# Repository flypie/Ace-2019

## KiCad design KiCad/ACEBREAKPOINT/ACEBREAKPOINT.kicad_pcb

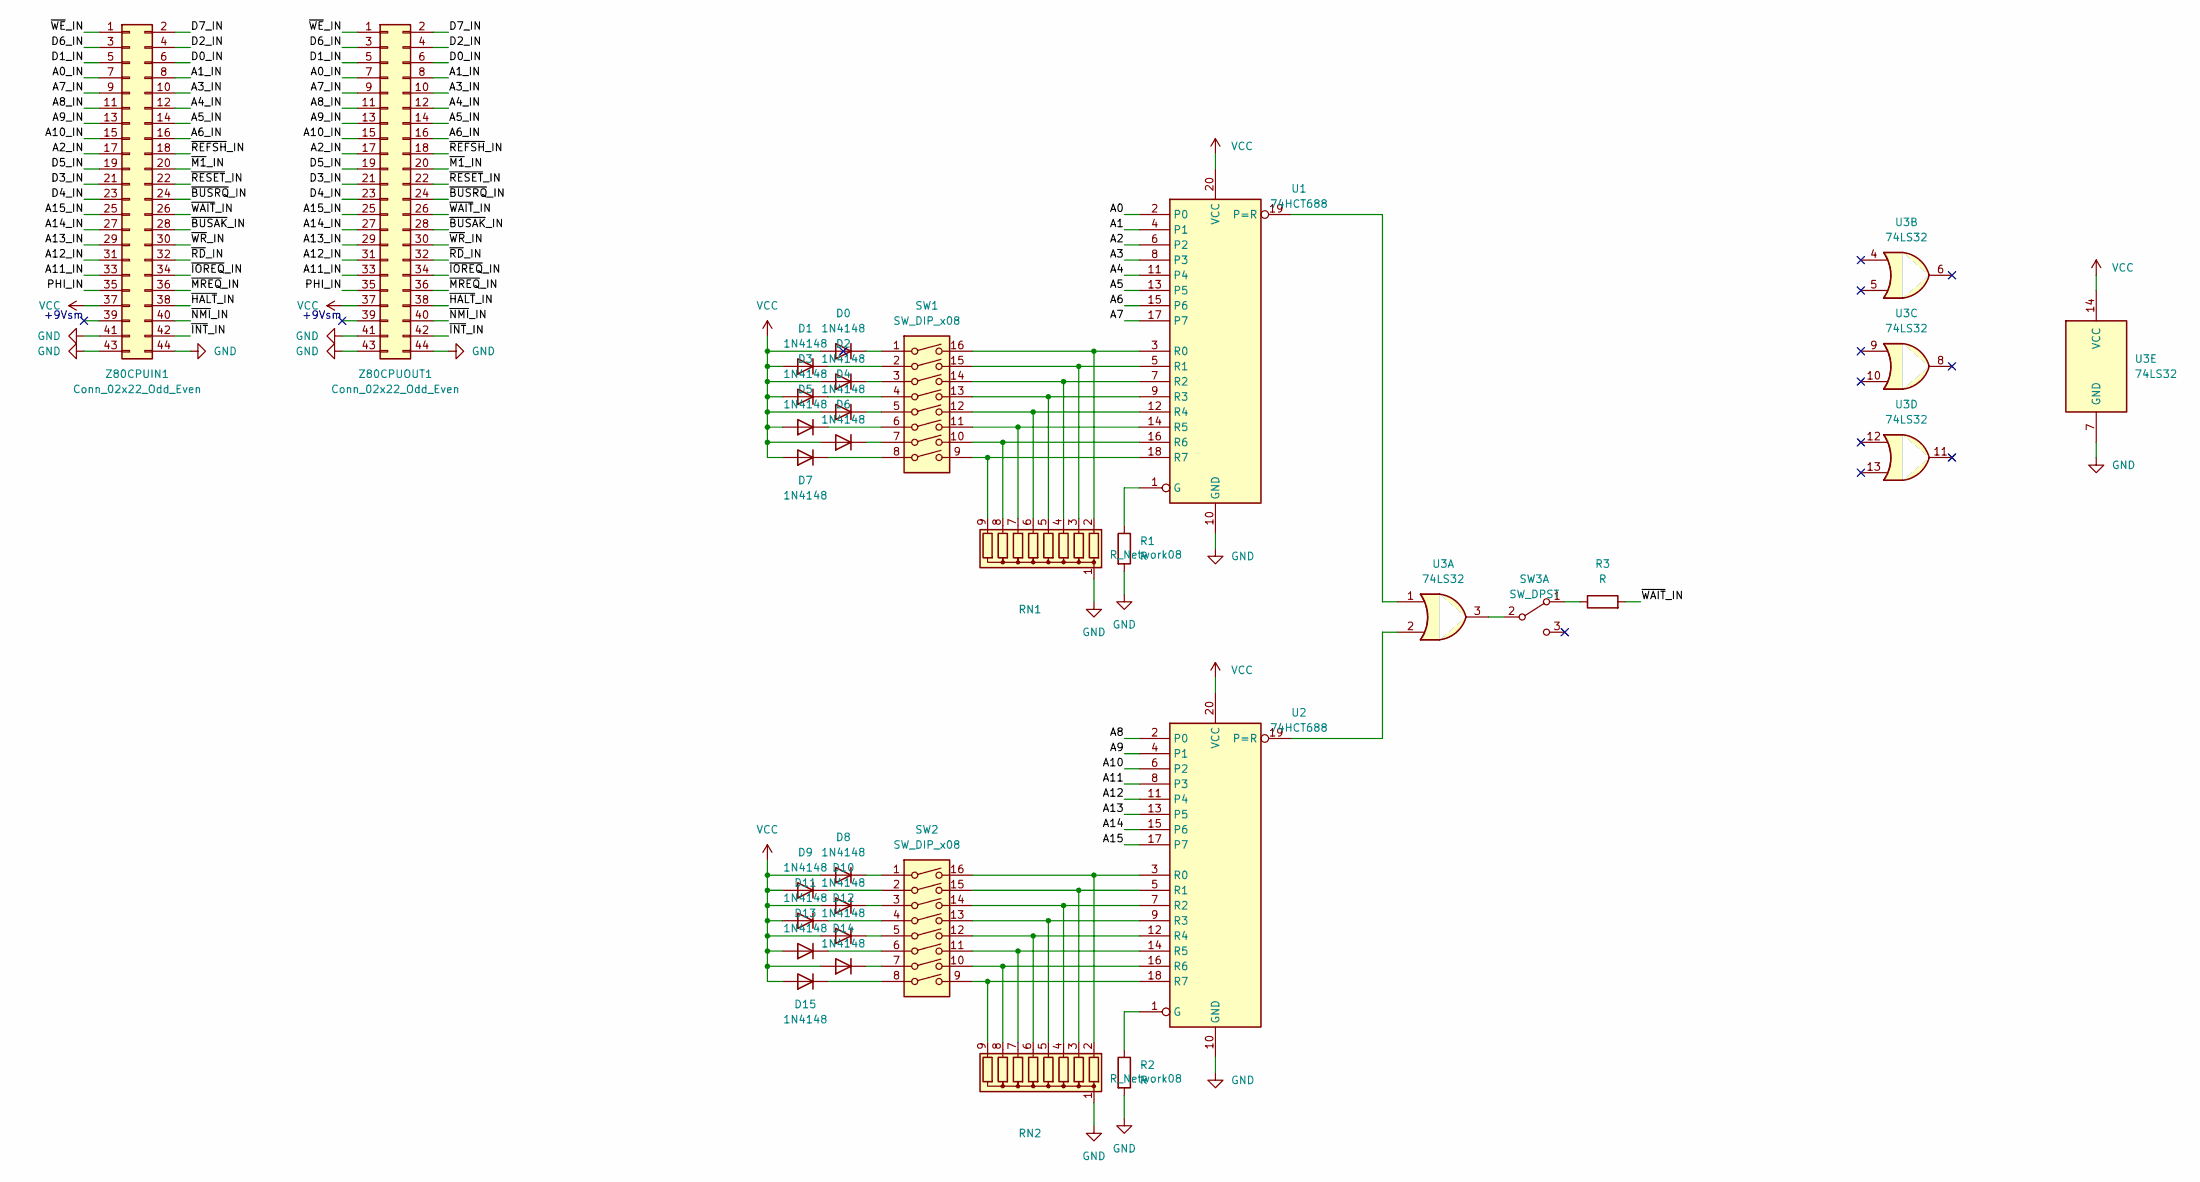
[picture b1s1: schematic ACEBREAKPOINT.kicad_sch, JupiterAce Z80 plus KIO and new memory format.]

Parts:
D0, D1, D2, D3, D4, D5, D6, D7, D8, D9, D10, D11, D12, D13, D14, D15: 1N4148; D_DO-35_SOD27_P2.54mm_Vertical_AnodeUp
R1, R2, R3: R; R_Axial_DIN0204_L3.6mm_D1.6mm_P1.90mm_Vertical
RN1, RN2: R_Network08; R_Array_SIP9
SW1, SW2: SW_DIP_x08; DIP-16_W7.62mm
SW3: SW_DPST; B13AP
U1, U2: 74HCT688; DIP-20_W7.62mm
U3: 74LS32; DIP-14_W7.62mm
Z80CPUIN1, Z80CPUOUT1: Conn_02x22_Odd_Even; PinHeader_2x22_P2.54mm_Vertical; Manufacturer_Part_Number M20-9721146

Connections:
/A0: U1.2 (P0)
/A0_IN: Z80CPUIN1.7, Z80CPUOUT1.7
/A1: U1.4 (P1)
/A1_IN: Z80CPUIN1.8, Z80CPUOUT1.8
/A2: U1.6 (P2)
/A2_IN: Z80CPUIN1.17, Z80CPUOUT1.17
/A3: U1.8 (P3)
/A3_IN: Z80CPUIN1.10, Z80CPUOUT1.10
/A4: U1.11 (P4)
/A4_IN: Z80CPUIN1.12, Z80CPUOUT1.12
/A5: U1.13 (P5)
/A5_IN: Z80CPUIN1.14, Z80CPUOUT1.14
/A6: U1.15 (P6)
/A6_IN: Z80CPUIN1.16, Z80CPUOUT1.16
/A7: U1.17 (P7)
/A7_IN: Z80CPUIN1.9, Z80CPUOUT1.9
/A8: U2.2 (P0)
/A8_IN: Z80CPUIN1.11, Z80CPUOUT1.11
/A9: U2.4 (P1)
/A9_IN: Z80CPUIN1.13, Z80CPUOUT1.13
/A10: U2.6 (P2)
/A10_IN: Z80CPUIN1.15, Z80CPUOUT1.15
/A11: U2.8 (P3)
/A11_IN: Z80CPUIN1.33, Z80CPUOUT1.33
/A12: U2.11 (P4)
/A12_IN: Z80CPUIN1.31, Z80CPUOUT1.31
/A13: U2.13 (P5)
/A13_IN: Z80CPUIN1.29, Z80CPUOUT1.29
/A14: U2.15 (P6)
/A14_IN: Z80CPUIN1.27, Z80CPUOUT1.27
/A15: U2.17 (P7)
/A15_IN: Z80CPUIN1.25, Z80CPUOUT1.25
/D0_IN: Z80CPUIN1.6, Z80CPUOUT1.6
/D1_IN: Z80CPUIN1.5, Z80CPUOUT1.5
/D2_IN: Z80CPUIN1.4, Z80CPUOUT1.4
/D3_IN: Z80CPUIN1.21, Z80CPUOUT1.21
/D4_IN: Z80CPUIN1.23, Z80CPUOUT1.23
/D5_IN: Z80CPUIN1.19, Z80CPUOUT1.19
/D6_IN: Z80CPUIN1.3, Z80CPUOUT1.3
/D7_IN: Z80CPUIN1.2, Z80CPUOUT1.2
/PHI_IN: Z80CPUIN1.35, Z80CPUOUT1.35
/~BUSAK_IN: Z80CPUIN1.28, Z80CPUOUT1.28
/~BUSRQ_IN: Z80CPUIN1.24, Z80CPUOUT1.24
/~HALT_IN: Z80CPUIN1.38, Z80CPUOUT1.38
/~INT_IN: Z80CPUIN1.42, Z80CPUOUT1.42
/~IOREQ_IN: Z80CPUIN1.34, Z80CPUOUT1.34
/~M1_IN: Z80CPUIN1.20, Z80CPUOUT1.20
/~MREQ_IN: Z80CPUIN1.36, Z80CPUOUT1.36
/~NMI_IN: Z80CPUIN1.40, Z80CPUOUT1.40
/~RD_IN: Z80CPUIN1.32, Z80CPUOUT1.32
/~REFSH_IN: Z80CPUIN1.18, Z80CPUOUT1.18
/~RESET_IN: Z80CPUIN1.22, Z80CPUOUT1.22
/~WAIT_IN: R3.2, Z80CPUIN1.26, Z80CPUOUT1.26
/~WE_IN: Z80CPUIN1.1, Z80CPUOUT1.1
/~WR_IN: Z80CPUIN1.30, Z80CPUOUT1.30
GND: R1.2, R2.2, RN1.1 (common), RN2.1 (common), U1.10 (GND), U2.10 (GND), U3.7 (GND), Z80CPUIN1.41, Z80CPUIN1.43, Z80CPUIN1.44, Z80CPUOUT1.41, Z80CPUOUT1.43, Z80CPUOUT1.44
unnamed: D0.1 (K), SW1.1
unnamed: D1.1 (K), SW1.2
unnamed: D2.1 (K), SW1.3
unnamed: D3.1 (K), SW1.4
unnamed: D4.1 (K), SW1.5
unnamed: D5.1 (K), SW1.6
unnamed: D6.1 (K), SW1.7
unnamed: D7.1 (K), SW1.8
unnamed: D8.1 (K), SW2.1
unnamed: D9.1 (K), SW2.2
unnamed: D10.1 (K), SW2.3
unnamed: D11.1 (K), SW2.4
unnamed: D12.1 (K), SW2.5
unnamed: D13.1 (K), SW2.6
unnamed: D14.1 (K), SW2.7
unnamed: D15.1 (K), SW2.8
unnamed: R1.1, U1.1 (G)
unnamed: R2.1, U2.1 (G)
unnamed: R3.1, SW3.1 (A)
unnamed: RN1.2 (R1), SW1.16, U1.3 (R0)
unnamed: RN1.3 (R2), SW1.15, U1.5 (R1)
unnamed: RN1.4 (R3), SW1.14, U1.7 (R2)
unnamed: RN1.5 (R4), SW1.13, U1.9 (R3)
unnamed: RN1.6 (R5), SW1.12, U1.12 (R4)
unnamed: RN1.7 (R6), SW1.11, U1.14 (R5)
unnamed: RN1.8 (R7), SW1.10, U1.16 (R6)
unnamed: RN1.9 (R8), SW1.9, U1.18 (R7)
unnamed: RN2.2 (R1), SW2.16, U2.3 (R0)
unnamed: RN2.3 (R2), SW2.15, U2.5 (R1)
unnamed: RN2.4 (R3), SW2.14, U2.7 (R2)
unnamed: RN2.5 (R4), SW2.13, U2.9 (R3)
unnamed: RN2.6 (R5), SW2.12, U2.12 (R4)
unnamed: RN2.7 (R6), SW2.11, U2.14 (R5)
unnamed: RN2.8 (R7), SW2.10, U2.16 (R6)
unnamed: RN2.9 (R8), SW2.9, U2.18 (R7)
unnamed: U1.19 (P=R), U3.1
unnamed: U2.19 (P=R), U3.2
unnamed: SW3.2 (B), U3.3
VCC: D0.2 (A), D1.2 (A), D2.2 (A), D3.2 (A), D4.2 (A), D5.2 (A), D6.2 (A), D7.2 (A), D8.2 (A), D9.2 (A), D10.2 (A), D11.2 (A), D12.2 (A), D13.2 (A), D14.2 (A), D15.2 (A), U1.20 (VCC), U2.20 (VCC), U3.14 (VCC), Z80CPUIN1.37, Z80CPUOUT1.37

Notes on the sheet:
+9Vsm

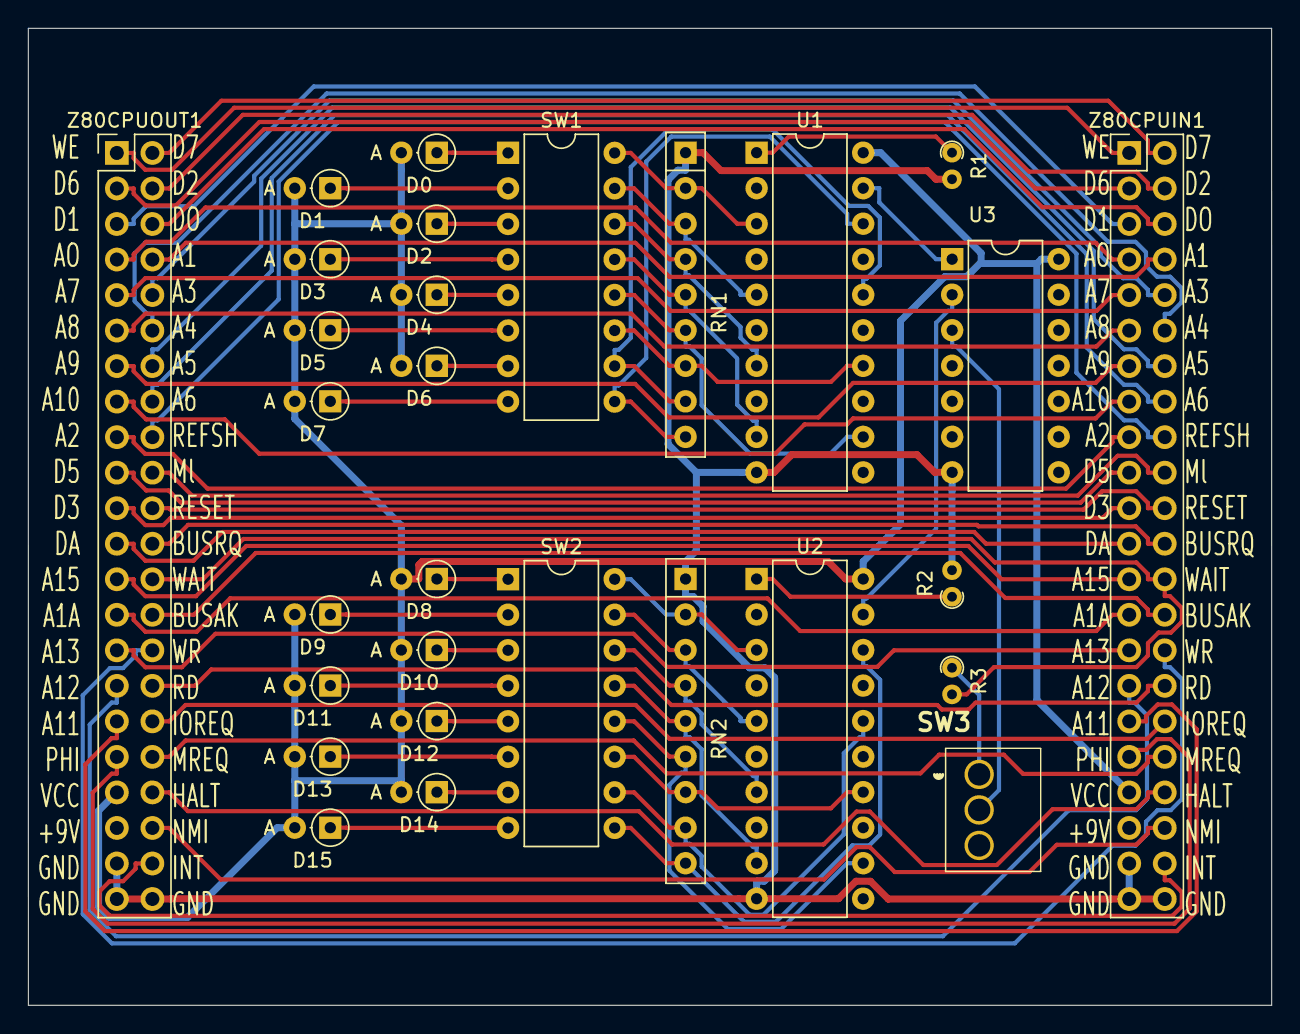
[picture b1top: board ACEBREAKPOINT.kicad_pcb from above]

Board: 2 copper layers, 88.9 x 69.8 mm, 29 parts (0 on the bottom side), 79 nets.

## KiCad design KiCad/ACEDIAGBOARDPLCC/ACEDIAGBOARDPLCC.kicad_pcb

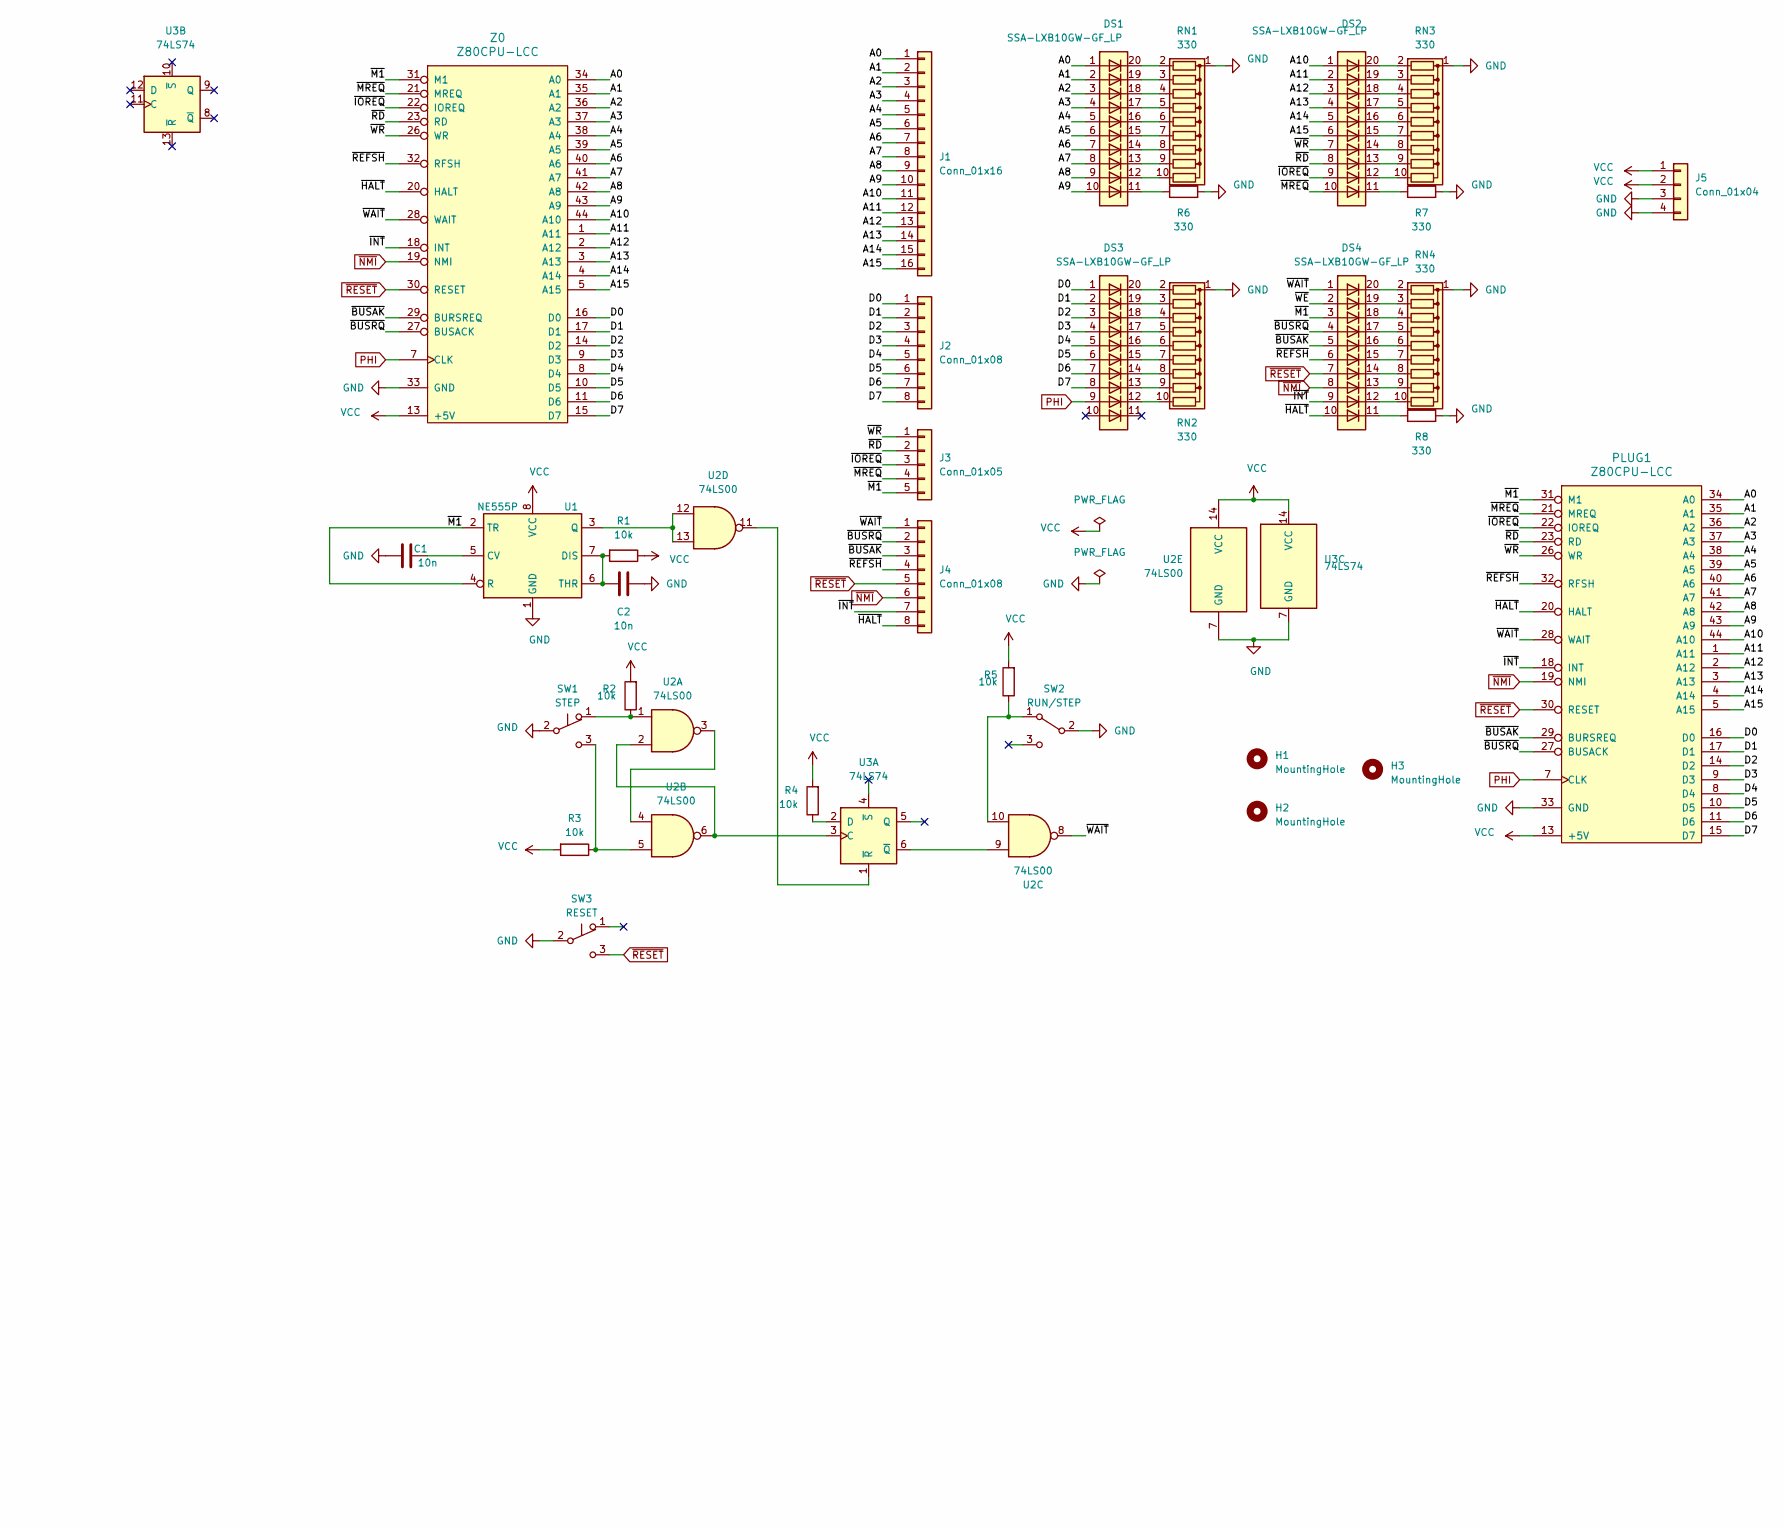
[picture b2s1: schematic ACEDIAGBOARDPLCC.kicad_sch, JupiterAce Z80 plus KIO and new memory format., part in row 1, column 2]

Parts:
C1, C2: 10n; C_Disc_D4.7mm_W2.5mm_P5.00mm
DS1, DS2, DS3, DS4: SSA-LXB10GW-GF_LP; 10_Bar_LED_Array_DIP-20_W7.62mm; Manufacturer_Part_Number SSA-LXB10GW-GF/LP; Mouser Part Number 696-SSA-LXB10GW
H1, H2, H3: MountingHole; MountingHole_3.5mm
J1: Conn_01x16; PinHeader_1x16_P2.54mm_Vertical
J2, J4: Conn_01x08; PinHeader_1x08_P2.54mm_Vertical
J3: Conn_01x05; PinHeader_1x05_P2.54mm_Vertical
J5: Conn_01x04; PinHeader_1x04_P2.54mm_Vertical
PLUG1: Z80CPU-LCC; PLCC-44_16.6x16.6mm_P1.27mm Mirror; Manufacturer_Part_Number W9382-ZC170
R1, R2, R3, R4, R5: 10k; R_Axial_DIN0204_L3.6mm_D1.6mm_P1.90mm_Vertical
R6, R7, R8: 330; R_Axial_DIN0204_L3.6mm_D1.6mm_P1.90mm_Vertical
RN1, RN2, RN3, RN4: 330; R_Array_SIP10; Manufacturer_Part_Number 4610X-101-331LF
SW1: STEP; ZMAXXXYYYZZZLC
SW2: RUN/STEP; B13AP
SW3: RESET; ZMAXXXYYYZZZLC
U1: NE555P; DIP-8_W7.62mm
U2: 74LS00; DIP-14_W7.62mm
U3: 74LS74; DIP-14_W7.62mm
Z0: Z80CPU-LCC; PLCC-44_THT-Socket; Manufacturer_Part_Number Z84C00

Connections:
/A0: DS1.1 (A), J1.1, PLUG1.34 (A0), Z0.34 (A0)
/A1: DS1.2 (A), J1.2, PLUG1.35 (A1), Z0.35 (A1)
/A2: DS1.3 (A), J1.3, PLUG1.36 (A2), Z0.36 (A2)
/A3: DS1.4 (A), J1.4, PLUG1.37 (A3), Z0.37 (A3)
/A4: DS1.5 (A), J1.5, PLUG1.38 (A4), Z0.38 (A4)
/A5: DS1.6 (A), J1.6, PLUG1.39 (A5), Z0.39 (A5)
/A6: DS1.7 (A), J1.7, PLUG1.40 (A6), Z0.40 (A6)
/A7: DS1.8 (A), J1.8, PLUG1.41 (A7), Z0.41 (A7)
/A8: DS1.9 (A), J1.9, PLUG1.42 (A8), Z0.42 (A8)
/A9: DS1.10 (A), J1.10, PLUG1.43 (A9), Z0.43 (A9)
/A10: DS2.1 (A), J1.11, PLUG1.44 (A10), Z0.44 (A10)
/A11: DS2.2 (A), J1.12, PLUG1.1 (A11), Z0.1 (A11)
/A12: DS2.3 (A), J1.13, PLUG1.2 (A12), Z0.2 (A12)
/A13: DS2.4 (A), J1.14, PLUG1.3 (A13), Z0.3 (A13)
/A14: DS2.5 (A), J1.15, PLUG1.4 (A14), Z0.4 (A14)
/A15: DS2.6 (A), J1.16, PLUG1.5 (A15), Z0.5 (A15)
/D0: DS3.1 (A), J2.1, PLUG1.16 (D0), Z0.16 (D0)
/D1: DS3.2 (A), J2.2, PLUG1.17 (D1), Z0.17 (D1)
/D2: DS3.3 (A), J2.3, PLUG1.14 (D2), Z0.14 (D2)
/D3: DS3.4 (A), J2.4, PLUG1.9 (D3), Z0.9 (D3)
/D4: DS3.5 (A), J2.5, PLUG1.8 (D4), Z0.8 (D4)
/D5: DS3.6 (A), J2.6, PLUG1.10 (D5), Z0.10 (D5)
/D6: DS3.7 (A), J2.7, PLUG1.11 (D6), Z0.11 (D6)
/D7: DS3.8 (A), J2.8, PLUG1.15 (D7), Z0.15 (D7)
/~BUSAK: DS4.5 (A), J4.3, PLUG1.29 (BURSREQ), Z0.29 (BURSREQ)
/~BUSRQ: DS4.4 (A), J4.2, PLUG1.27 (BUSACK), Z0.27 (BUSACK)
/~HALT: DS4.10 (A), J4.8, PLUG1.20 (HALT), Z0.20 (HALT)
/~INT: DS4.9 (A), J4.7, PLUG1.18 (INT), Z0.18 (INT)
/~IOREQ: DS2.9 (A), J3.3, PLUG1.22 (IOREQ), Z0.22 (IOREQ)
/~M1: DS4.3 (A), J3.5, PLUG1.31 (M1), U1.2 (TR), U1.4 (R), Z0.31 (M1)
/~MREQ: DS2.10 (A), J3.4, PLUG1.21 (MREQ), Z0.21 (MREQ)
/~RD: DS2.8 (A), J3.2, PLUG1.23 (RD), Z0.23 (RD)
/~REFSH: DS4.6 (A), J4.4, PLUG1.32 (RFSH), Z0.32 (RFSH)
/~WAIT: DS4.1 (A), J4.1, PLUG1.28 (WAIT), U2.8, Z0.28 (WAIT)
/~WE: DS4.2 (A)
/~WR: DS2.7 (A), J3.1, PLUG1.26 (WR), Z0.26 (WR)
GND: C1.2, C2.1, J5.3, J5.4, PLUG1.33 (GND), R6.2, R7.2, R8.2, RN1.1 (common), RN2.1 (common), RN3.1 (common), RN4.1 (common), SW1.2 (B), SW2.2 (B), SW3.2 (B), U1.1 (GND), U2.7 (GND), U3.7 (GND), Z0.33 (GND)
unnamed: C1.1, U1.5 (CV)
unnamed: C2.2, R1.2, U1.6 (THR), U1.7 (DIS)
unnamed: DS1.11 (K), R6.1
unnamed: DS1.12 (K), RN1.10 (R9)
unnamed: DS1.13 (K), RN1.9 (R8)
unnamed: DS1.14 (K), RN1.8 (R7)
unnamed: DS1.15 (K), RN1.7 (R6)
unnamed: DS1.16 (K), RN1.6 (R5)
unnamed: DS1.17 (K), RN1.5 (R4)
unnamed: DS1.18 (K), RN1.4 (R3)
unnamed: DS1.19 (K), RN1.3 (R2)
unnamed: DS1.20 (K), RN1.2 (R1)
unnamed: DS2.11 (K), R7.1
unnamed: DS2.12 (K), RN3.10 (R9)
unnamed: DS2.13 (K), RN3.9 (R8)
unnamed: DS2.14 (K), RN3.8 (R7)
unnamed: DS2.15 (K), RN3.7 (R6)
unnamed: DS2.16 (K), RN3.6 (R5)
unnamed: DS2.17 (K), RN3.5 (R4)
unnamed: DS2.18 (K), RN3.4 (R3)
unnamed: DS2.19 (K), RN3.3 (R2)
unnamed: DS2.20 (K), RN3.2 (R1)
unnamed: DS3.12 (K), RN2.10 (R9)
unnamed: DS3.13 (K), RN2.9 (R8)
unnamed: DS3.14 (K), RN2.8 (R7)
unnamed: DS3.15 (K), RN2.7 (R6)
unnamed: DS3.16 (K), RN2.6 (R5)
unnamed: DS3.17 (K), RN2.5 (R4)
unnamed: DS3.18 (K), RN2.4 (R3)
unnamed: DS3.19 (K), RN2.3 (R2)
unnamed: DS3.20 (K), RN2.2 (R1)
unnamed: DS4.11 (K), R8.1
unnamed: DS4.12 (K), RN4.10 (R9)
unnamed: DS4.13 (K), RN4.9 (R8)
unnamed: DS4.14 (K), RN4.8 (R7)
unnamed: DS4.15 (K), RN4.7 (R6)
unnamed: DS4.16 (K), RN4.6 (R5)
unnamed: DS4.17 (K), RN4.5 (R4)
unnamed: DS4.18 (K), RN4.4 (R3)
unnamed: DS4.19 (K), RN4.3 (R2)
unnamed: DS4.20 (K), RN4.2 (R1)
unnamed: R2.1, SW1.1 (A), U2.1
unnamed: R3.1, SW1.3 (C), U2.5
unnamed: R4.1, U3.2 (D)
unnamed: R5.1, SW2.1 (A), U2.10
unnamed: U1.3 (Q), U2.12, U2.13
unnamed: U2.2, U2.6, U3.3 (C)
unnamed: U2.3, U2.4
unnamed: U2.9, U3.6 (~Q)
unnamed: U2.11, U3.1 (~R)
PHI: DS3.9 (A), PLUG1.7 (CLK), Z0.7 (CLK)
VCC: J5.1, J5.2, PLUG1.13 (+5V), R1.1, R2.2, R3.2, R4.2, R5.2, U1.8 (VCC), U2.14 (VCC), U3.14 (VCC), Z0.13 (+5V)
~NMI: DS4.8 (A), J4.6, PLUG1.19 (NMI), Z0.19 (NMI)
~RESET: DS4.7 (A), J4.5, PLUG1.30 (RESET), SW3.3 (C), Z0.30 (RESET)

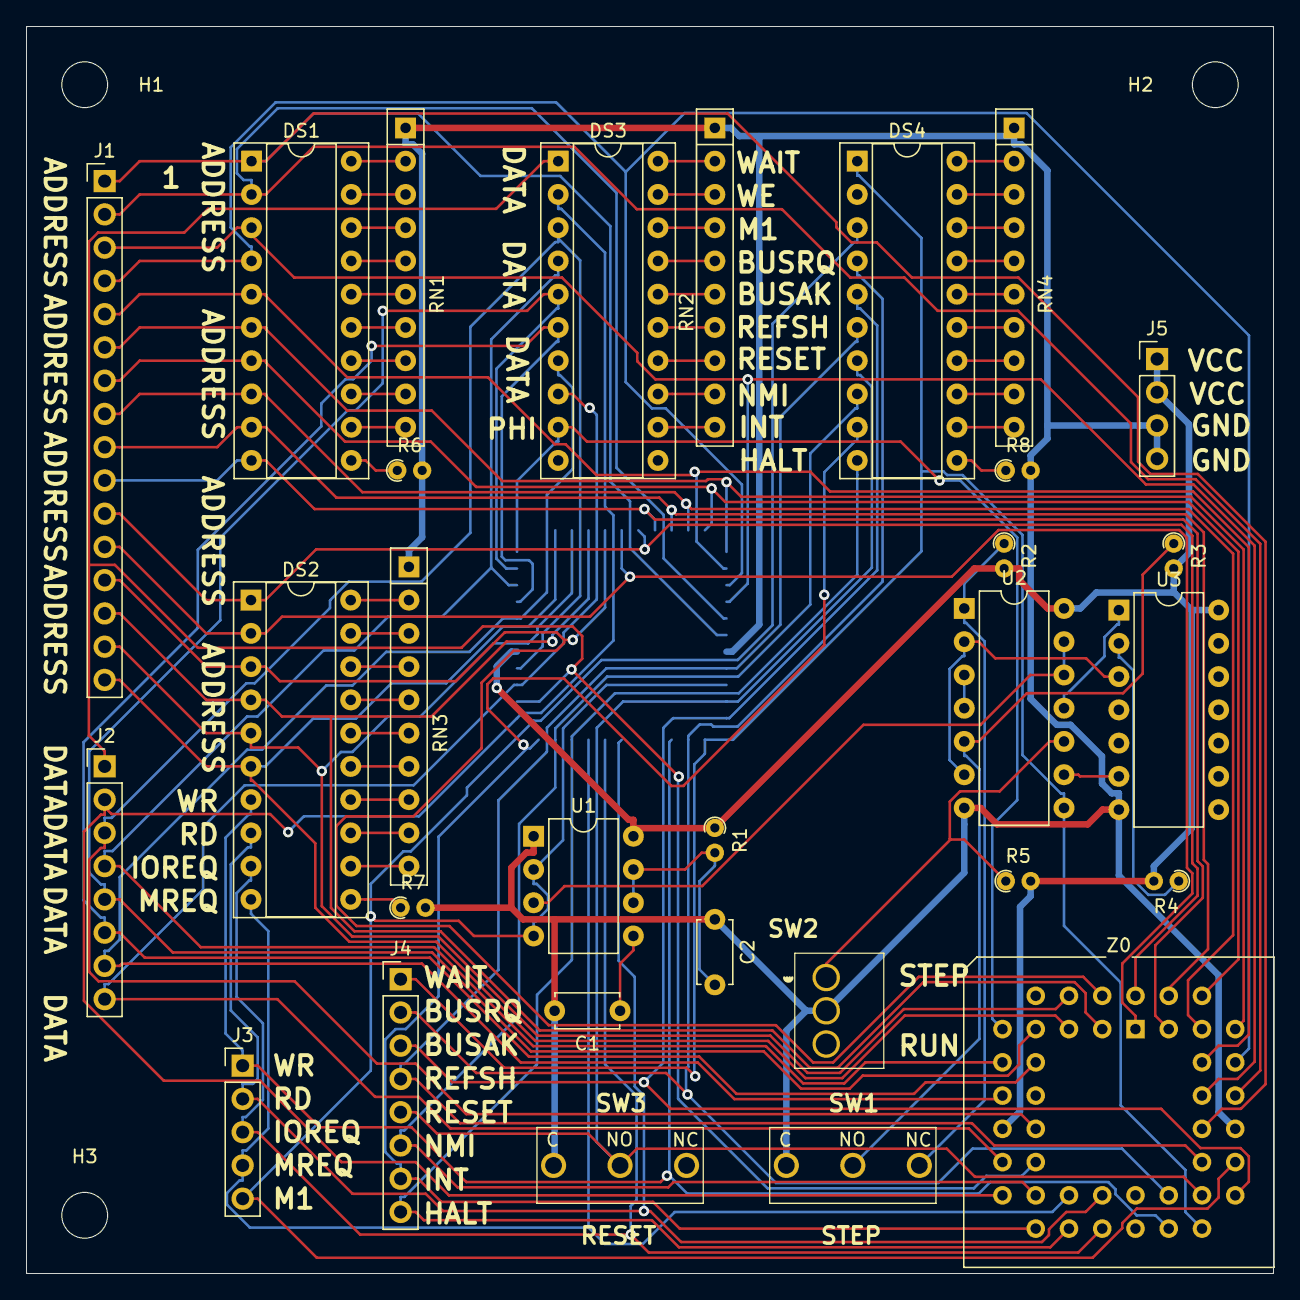
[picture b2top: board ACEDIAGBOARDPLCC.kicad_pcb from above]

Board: 2 copper layers, 95.2 x 95.2 mm, 34 parts (1 on the bottom side), 90 nets.

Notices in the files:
KiCad/ACEBREAKPOINT/ACEBREAKPOINT.kicad_sch:
https://creativecommons.org/licenses/by-nc-sa/4.0
This work is licensed under a Creative Commons
